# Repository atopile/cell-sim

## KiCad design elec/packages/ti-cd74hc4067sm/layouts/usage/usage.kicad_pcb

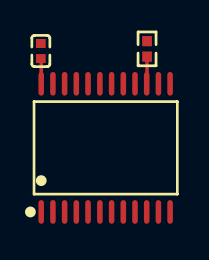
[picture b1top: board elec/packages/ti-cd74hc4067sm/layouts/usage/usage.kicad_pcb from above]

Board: 2 copper layers, 3 parts (0 on the bottom side), 3 nets.

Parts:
C1: 1F; C0402
R1: 10000Ω; R0402
U1: SSOP-24_L8.1-W5.3-P0.65-LS7.8-BL

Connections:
hv: C1.1, U1.8, U1.24
lv: C1.2, R1.1, U1.9, U1.12
nE: R1.2, U1.15

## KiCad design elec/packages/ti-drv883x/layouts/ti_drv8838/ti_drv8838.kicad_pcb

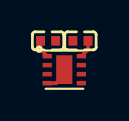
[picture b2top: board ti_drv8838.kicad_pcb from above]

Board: 2 copper layers, 3 parts (0 on the bottom side), 3 nets.

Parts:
C1, C2: 100nF; C0402
U1: WSON-8_L2.0-W2.0-P0.50-TL-EP

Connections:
hv: C1.1, U1.8
lv: C1.2, C2.2, U1.4, U1.9
motor_power_decoupling_capacitor-power-hv: C2.1, U1.1

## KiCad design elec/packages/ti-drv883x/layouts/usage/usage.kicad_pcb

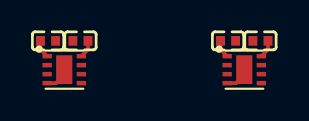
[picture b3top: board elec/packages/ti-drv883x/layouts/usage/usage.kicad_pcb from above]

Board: 2 copper layers, 6 parts (0 on the bottom side), 6 nets.

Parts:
C1, C2, C3, C4: 100nF; C0402
U1, U2: WSON-8_L2.0-W2.0-P0.50-TL-EP

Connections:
5: U1.5, U2.5
6: U1.6, U2.6
7: U1.7, U2.7
hv: C1.1, C3.1, U1.8, U2.8
lv: C1.2, C2.2, C3.2, C4.2, U1.4, U1.9, U2.4, U2.9
power-hv: C2.1, C4.1, U1.1, U2.1

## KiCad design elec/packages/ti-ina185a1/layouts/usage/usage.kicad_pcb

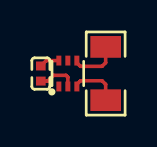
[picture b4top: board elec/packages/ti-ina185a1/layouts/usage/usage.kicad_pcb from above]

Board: 2 copper layers, 3 parts (0 on the bottom side), 4 nets.

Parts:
C1: 100nF; C0402
R1: 10mΩ; R1206
U1: SOT-563_L1.6-W1.2-P0.50-LS1.6-BL

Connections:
hv: C1.1, U1.6
load_power_P: R1.1, U1.3
lv: C1.2, U1.2, U1.5
power_to_load_N: R1.2, U1.4

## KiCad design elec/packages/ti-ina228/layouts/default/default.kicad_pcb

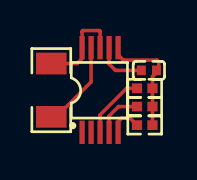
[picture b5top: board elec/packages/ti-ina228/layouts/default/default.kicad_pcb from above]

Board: 2 copper layers, 6 parts (0 on the bottom side), 7 nets.

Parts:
C1: 100nF; C0402
R1: 150mΩ; R1206
R2, R3, R4: 10kΩ; R0402
U1: VSSOP-10_L3.0-W3.0-P0.50-LS4.9-BL

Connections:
ALERT: R4.1, U1.3
SCL: R2.1, U1.5
SDA: R3.1, U1.4
hv: C1.1, R2.2, R3.2, R4.2, U1.6
lv: C1.2, U1.1, U1.2, U1.7
power_in_P: R1.1, U1.8, U1.10
power_out_N: R1.2, U1.9

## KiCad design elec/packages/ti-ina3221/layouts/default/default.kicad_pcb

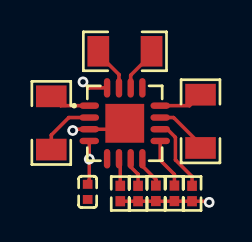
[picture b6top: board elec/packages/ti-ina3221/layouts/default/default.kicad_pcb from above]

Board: 2 copper layers, 10 parts (0 on the bottom side), 13 nets.

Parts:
C1: 100nF; C0402
R1, R2, R3: 150mΩ; R1206
R4, R5, R6, R7, R8: 10kΩ; R0402
U1: QFN-16_L4.0-W4.0-P0.65-TL-EP2.2

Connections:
CRITICAL: R4.2, U1.9
PV: R7.2, U1.10
SCL: R5.2, U1.6
SDA: R6.2, U1.7
WARNING: R8.2, U1.8
channels[1]-power_in-power_in_P: R2.1, U1.15
channels[1]-power_out-power_out_N: R2.2, U1.14
channels[2]-power_in-power_in_P: R3.1, U1.2
channels[2]-power_out-power_out_N: R3.2, U1.1
hv: C1.1, R4.1, R5.1, R6.1, R7.1, R8.1, U1.4, U1.16
lv: C1.2, U1.3, U1.17
power_in_P: R1.1, U1.12
power_out_N: R1.2, U1.11
